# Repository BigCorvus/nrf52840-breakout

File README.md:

# nrf52840-breakout
Simple nrf52840 breakout board for the cheap an common Holyiot_18010 module. Includes USB connector.

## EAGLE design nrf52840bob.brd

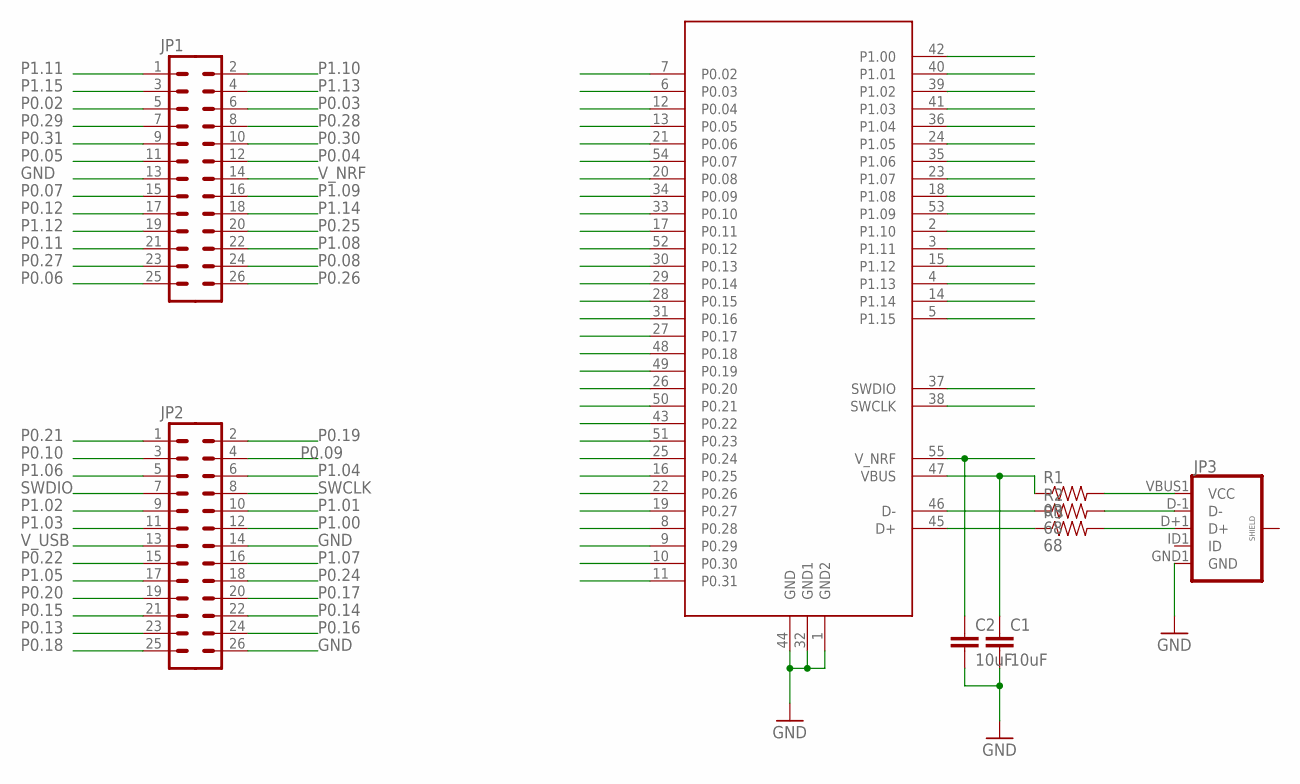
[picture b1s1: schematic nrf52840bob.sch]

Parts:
C1, C2: 10uF; 0603-CAP
JP1, JP2: M13X22X13; 2X13
JP3: USB_MICROB_PLUGCONN-11752; USB-B-MICRO-SMD_V03
R1: 0R; 0603-RES
R2, R3: 68; 0603-RES
U$1: NRF52840; NRF52840MOD

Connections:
GND: C1.2, C2.2, JP1.13, JP2.14, JP2.26, JP3.GND1 (GND), U$1.1 (GND2), U$1.32 (GND1), U$1.44 (GND)
unnamed: R2.1, U$1.46 (D-)
unnamed: R3.1, U$1.45 (D+)
unnamed: JP3.D-1 (D-), R2.2
unnamed: JP3.D+1 (D+), R3.2
unnamed: C1.1, R1.1, U$1.47 (VBUS)
P0.02: JP1.5, U$1.7 (P0.02)
P0.03: JP1.6, U$1.6 (P0.03)
P0.04: JP1.12, U$1.12 (P0.04)
P0.05: JP1.11, U$1.13 (P0.05)
P0.06: JP1.25, U$1.21 (P0.06)
P0.07: JP1.15, U$1.54 (P0.07)
P0.08: JP1.24, U$1.20 (P0.08)
P0.09: JP2.4, U$1.34 (P0.09)
P0.10: JP2.3, U$1.33 (P0.10)
P0.11: JP1.21, U$1.17 (P0.11)
P0.12: JP1.17, U$1.52 (P0.12)
P0.13: JP2.23, U$1.30 (P0.13)
P0.14: JP2.22, U$1.29 (P0.14)
P0.15: JP2.21, U$1.28 (P0.15)
P0.16: JP2.24, U$1.31 (P0.16)
P0.17: JP2.20, U$1.27 (P0.17)
P0.18: JP2.25, U$1.48 (P0.18)
P0.19: JP2.2, U$1.49 (P0.19)
P0.20: JP2.19, U$1.26 (P0.20)
P0.21: JP2.1, U$1.50 (P0.21)
P0.22: JP2.15, U$1.43 (P0.22)
P0.23: U$1.51 (P0.23)
P0.24: JP2.18, U$1.25 (P0.24)
P0.25: JP1.20, U$1.16 (P0.25)
P0.26: JP1.26, U$1.22 (P0.26)
P0.27: JP1.23, U$1.19 (P0.27)
P0.28: JP1.8, U$1.8 (P0.28)
P0.29: JP1.7, U$1.9 (P0.29)
P0.30: JP1.10, U$1.10 (P0.30)
P0.31: JP1.9, U$1.11 (P0.31)
P1.00: JP2.12, U$1.42 (P1.00)
P1.01: JP2.10, U$1.40 (P1.01)
P1.02: JP2.9, U$1.39 (P1.02)
P1.03: JP2.11, U$1.41 (P1.03)
P1.04: JP2.6, U$1.36 (P1.04)
P1.05: JP2.17, U$1.24 (P1.05)
P1.06: JP2.5, U$1.35 (P1.06)
P1.07: JP2.16, U$1.23 (P1.07)
P1.08: JP1.22, U$1.18 (P1.08)
P1.09: JP1.16, U$1.53 (P1.09)
P1.10: JP1.2, U$1.2 (P1.10)
P1.11: JP1.1, U$1.3 (P1.11)
P1.12: JP1.19, U$1.15 (P1.12)
P1.13: JP1.4, U$1.4 (P1.13)
P1.14: JP1.18, U$1.14 (P1.14)
P1.15: JP1.3, U$1.5 (P1.15)
SWCLK: JP2.8, U$1.38 (SWCLK)
SWDIO: JP2.7, U$1.37 (SWDIO)
V_NRF: C2.1, JP1.14, U$1.55 (V_NRF)
V_USB: JP2.13, JP3.VBUS1 (VCC), R1.2

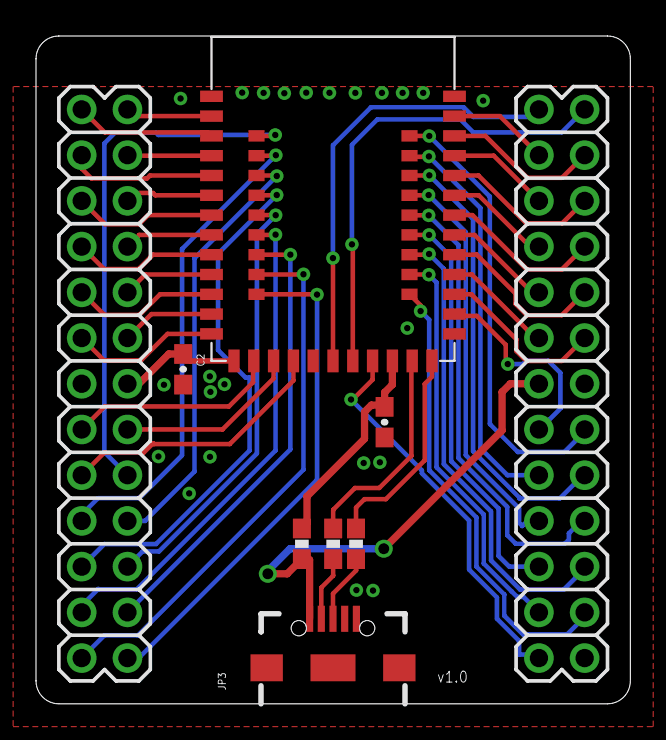
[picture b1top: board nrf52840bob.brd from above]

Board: 2 copper layers, 33.0 x 37.1 mm, 9 parts (0 on the bottom side), 55 nets.

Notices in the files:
parts and their libraries:
SparkFun-Connectors: Licensing: Creative Commons ShareAlike 4.0 International - https://creativecommons.org/licenses/by-sa/4.0
